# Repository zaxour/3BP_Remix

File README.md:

# 3BP_Remix
Modified version of Tian Feng/dB_Electronics triple bypass v2 board

Incorporates 5.6k pull up resistors for the RGB lines, as Model 1 3BP installs lift the VDP pins to isolate them from the Genesis/MD PCB. Based on research by Tian Feng, and subsequently verified by myself by looking at all available schematics for the Model 1 Genesis/MD, this causes a loss of fidelity in color transitions.

The positioning of the Mini DIN has also been adjusted to fit alongside the Model 1's existing video connector.

Files provided are compatible with Autodesk Eagle (Fusion 360).

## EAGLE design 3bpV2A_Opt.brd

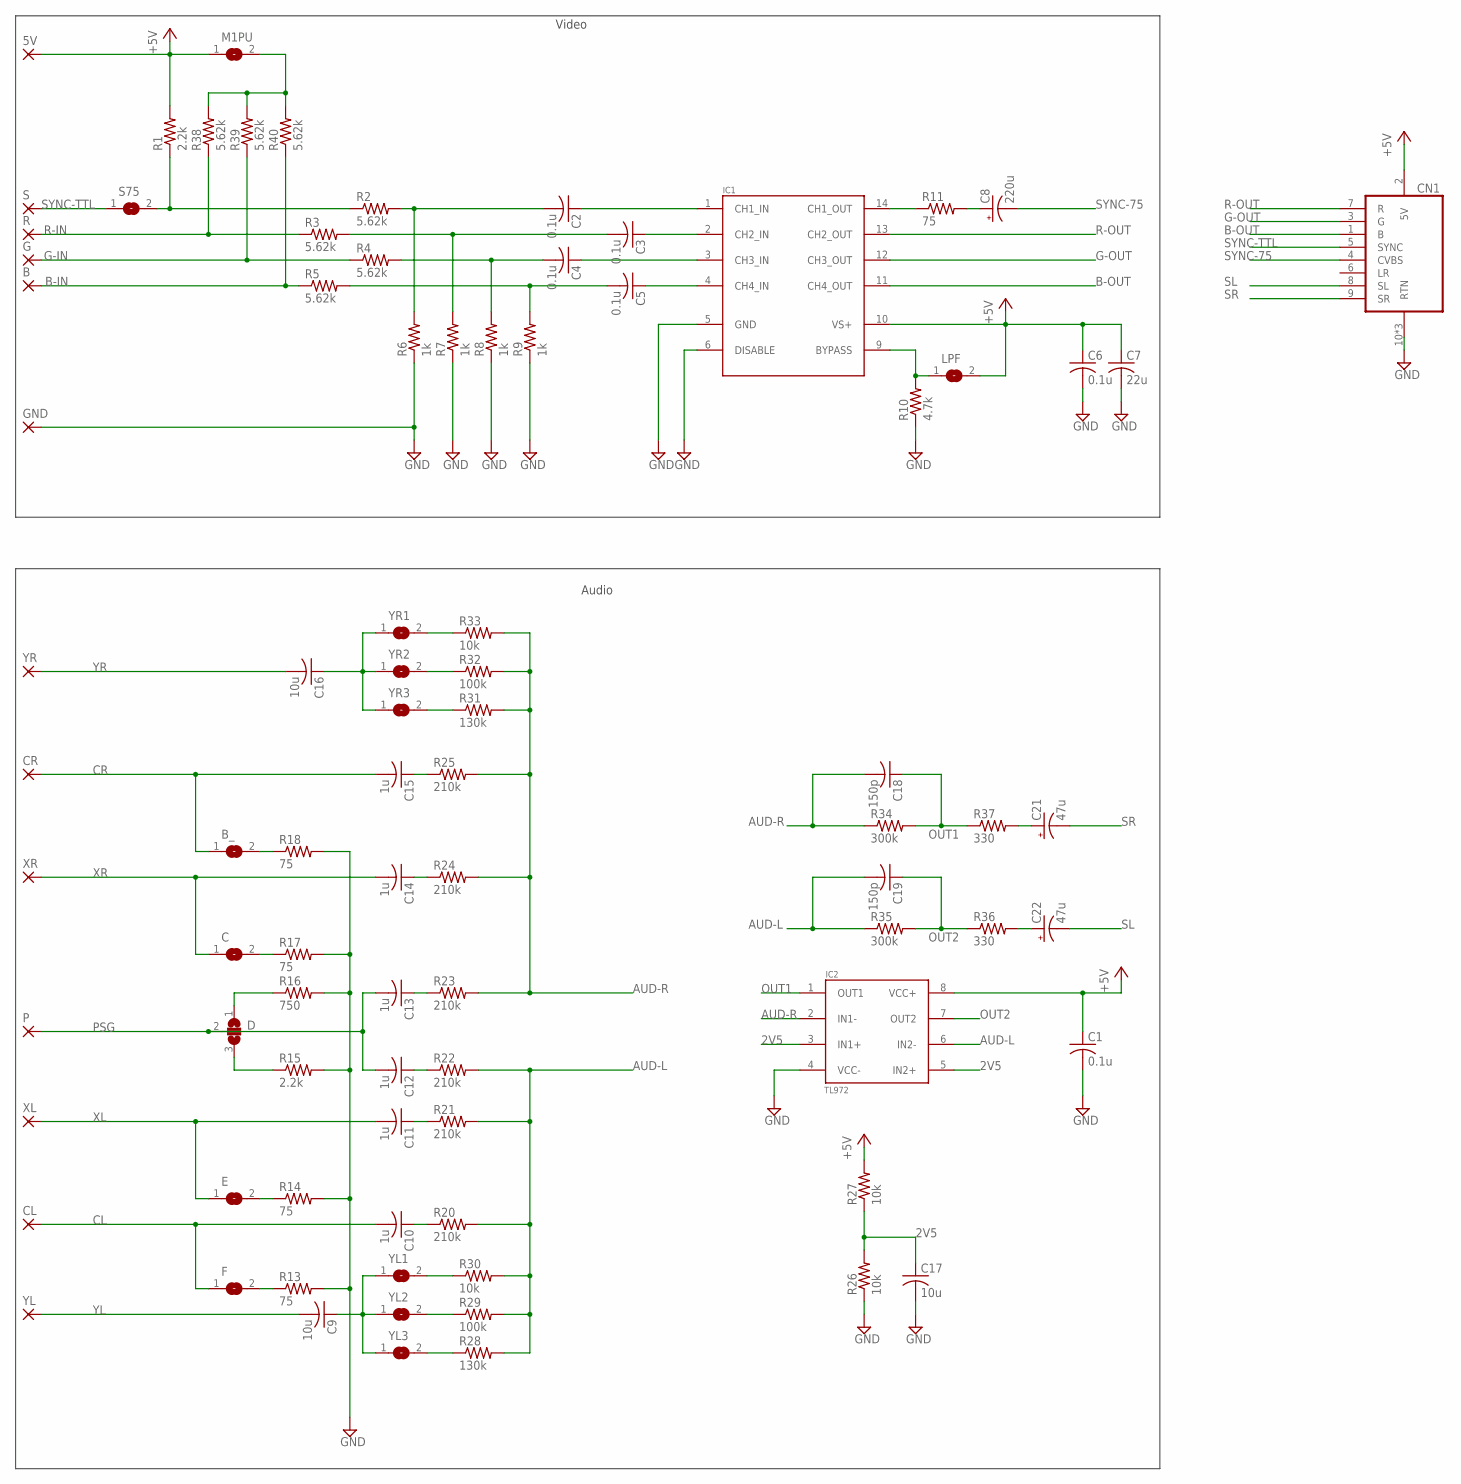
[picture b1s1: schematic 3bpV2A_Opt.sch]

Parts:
5V: SMD2; SMD1,27-2,54
B: SMD2; SMD1,27-2,54
B_: SMD_J; SJ
C: SMD_J; SJ
C1, C2, C3, C4, C5, C6: 0.1u; C0603
C7: 22u; C1206
C8: 220u; CT3528
C9, C16: 10u; C0805
C10, C11, C12, C13, C14, C15: 1u; C0603
C17: 10u; C1206
C18, C19: 150p; C0603
C21, C22: 47u; CT3528
CL: SMD2; SMD1,27-2,54
CN1: MD-90SM; MD90SM
CR: SMD2; SMD1,27-2,54
D: SMD_J2; SJ_2
E: SMD_J; SJ
F: SMD_J; SJ
G: SMD2; SMD1,27-2,54
GND: SMD2; SMD1,27-2,54
IC1: THS7374IPWR; TSSOP14
IC2: TL972; SOIC8
LPF: SMD_J; SJ
M1PU: SMD_J; SJ
P: SMD2; SMD1,27-2,54
R: SMD2; SMD1,27-2,54
R1, R15: 2.2k; R0603
R2, R3, R4, R5, R38, R39, R40: 5.62k; R0603
R6, R7, R8, R9: 1k; R0603
R10: 4.7k; R0603
R11, R13, R14, R17, R18: 75; R0603
R16: 750; R0603
R20, R21, R22, R23, R24, R25: 210k; R0603
R26, R27, R30, R33: 10k; R0603
R28, R31: 130k; R0603
R29, R32: 100k; R0603
R34, R35: 300k; R0603
R36, R37: 330; R0603
S: SMD2; SMD1,27-2,54
S75: SMD_J; SJ
XL: SMD2; SMD1,27-2,54
XR: SMD2; SMD1,27-2,54
YL: SMD2; SMD1,27-2,54
YL1, YL2, YL3: SMD_J; SJ
YR: SMD2; SMD1,27-2,54
YR1, YR2, YR3: SMD_J; SJ

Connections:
2V5: C17.1, IC2.3 (IN1+), IC2.5 (IN2+), R26.2, R27.1
+5V: 5V.1, C1.1, C6.1, C7.1, CN1.2 (5V), IC1.10 (VS+), IC2.8 (VCC+), LPF.2, M1PU.1, R1.2, R27.2
AUD-L: C19.2, IC2.6 (IN2-), R20.2, R21.2, R22.2, R28.2, R29.2, R30.2, R35.1
AUD-R: C18.2, IC2.2 (IN1-), R23.2, R24.2, R25.2, R31.2, R32.2, R33.2, R34.1
B-IN: B.1, R5.1, R40.1
B-OUT: CN1.1 (B), IC1.11 (CH4_OUT)
CL: C10.2, CL.1, F.1
CR: B_.1, C15.2, CR.1
G-IN: G.1, R4.1, R39.1
G-OUT: CN1.3 (G), IC1.12 (CH3_OUT)
GND: C1.2, C6.2, C7.2, C17.2, CN1.10 (RTN), CN1.11 (RTN), CN1.12 (RTN), GND.1, IC1.5 (GND), IC1.6 (DISABLE), IC2.4 (VCC-), R6.1, R7.1, R8.1, R9.1, R10.1, R13.2, R14.2, R15.2, R16.2, R17.2, R18.2, R26.1
unnamed: C2.2, R2.2, R6.2
unnamed: C2.1, IC1.1 (CH1_IN)
unnamed: C3.2, R3.2, R7.2
unnamed: C3.1, IC1.2 (CH2_IN)
unnamed: C4.2, R4.2, R8.2
unnamed: C4.1, IC1.3 (CH3_IN)
unnamed: C5.1, IC1.4 (CH4_IN)
unnamed: C5.2, R5.2, R9.2
unnamed: IC1.9 (BYPASS), LPF.1, R10.2
unnamed: M1PU.2, R38.2, R39.2, R40.2
unnamed: B_.2, R18.1
unnamed: R1.1, R2.1, S75.2
unnamed: IC1.14 (CH1_OUT), R11.1
unnamed: C8.+, R11.2
unnamed: C16.1, YR1.1, YR2.1, YR3.1
unnamed: R33.1, YR1.2
unnamed: R32.1, YR2.2
unnamed: R31.1, YR3.2
unnamed: E.2, R14.1
unnamed: C15.1, R25.1
unnamed: C.2, R17.1
unnamed: C14.1, R24.1
unnamed: D.3, R15.1
unnamed: D.1, R16.1
unnamed: C13.1, R23.1
unnamed: C12.1, R22.1
unnamed: C11.1, R21.1
unnamed: F.2, R13.1
unnamed: C10.1, R20.1
unnamed: C9.1, YL1.1, YL2.1, YL3.1
unnamed: R30.1, YL1.2
unnamed: R29.1, YL2.2
unnamed: R28.1, YL3.2
unnamed: C22.+, R36.2
unnamed: C21.+, R37.2
OUT1: C18.1, IC2.1 (OUT1), R34.2, R37.1
OUT2: C19.1, IC2.7 (OUT2), R35.2, R36.1
PSG: C12.2, C13.2, D.2, P.1
R-IN: R.1, R3.1, R38.1
R-OUT: CN1.7 (R), IC1.13 (CH2_OUT)
SL: C22.-, CN1.8 (SL)
SR: C21.-, CN1.9 (SR)
SYNC-75: C8.-, CN1.4 (CVBS)
SYNC-TTL: CN1.5 (SYNC), S.1, S75.1
XL: C11.2, E.1, XL.1
XR: C.1, C14.2, XR.1
YL: C9.2, YL.1
YR: C16.2, YR.1

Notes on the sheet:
Audio
Video

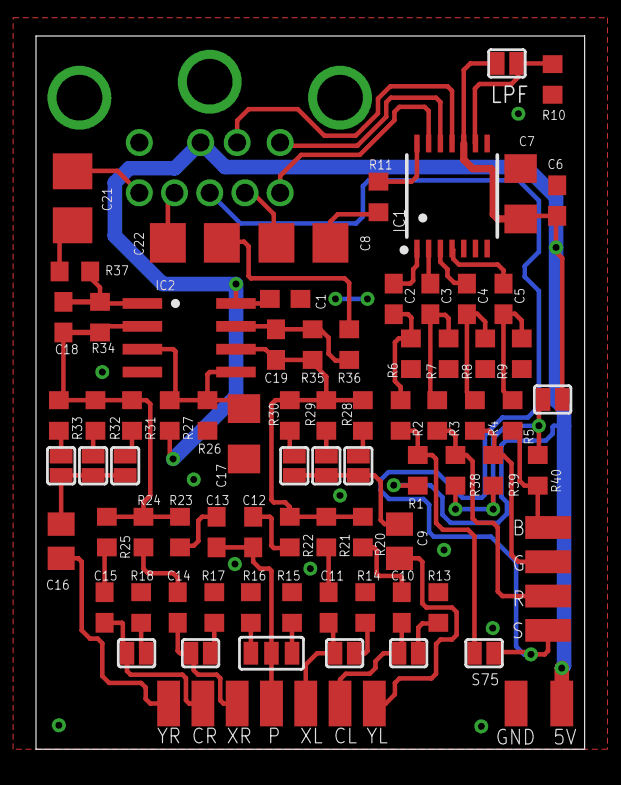
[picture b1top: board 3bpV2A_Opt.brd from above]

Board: 2 copper layers, 30.5 x 39.6 mm, 89 parts (1 on the bottom side), 59 nets.

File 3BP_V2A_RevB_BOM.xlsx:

Qty | Value | Package | Parts
6 | 0.1u | C0603 | C1, C2, C3, C4, C5, C6 | v
2 | 150p | C0603 | C18, C19 | v
6 | 1u | C0603 | C10, C11, C12, C13, C14, C15 | v
2 | 10u | C0805 | C9, C16 | v
1 | 10u | C1206 | C17 | v
1 | 22u | C1206 | C7 | v
1 | 220u | CT3528 | C8 | v
2 | 47u | CT3528 | C21, C22 | v
1 | MD-90SM | MD90SM | CN1
2 | 100k | R0603 | R29, R32 | v
4 | 10k | R0603 | R26, R27, R30, R33 | v
2 | 130k | R0603 | R28, R31 | v
4 | 1k | R0603 | R6, R7, R8, R9 | v
2 | 2.2k | R0603 | R1, R15 | v
6 | 210k | R0603 | R20, R21, R22, R23, R24, R25 | v
2 | 300k | R0603 | R34, R35 | v
2 | 330 | R0603 | R36, R37 | v
1 | 4.7k | R0603 | R10 | v
7 | 5.62k | R0603 | R2, R3, R4, R5, R38, R39, R40 | v
5 | 75 | R0603 | R11, R13, R14, R17, R18 | v
1 | 750 | R0603 | R16 | v
1 | TL972 | SOIC8 | IC2 | v
1 | THS7374IPWR | TSSOP14 | IC1
https://www.digikey.com/short/43w8t24t

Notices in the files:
3bpV2A_Opt.brd:
Licensed under
CERN OHL v1.2
